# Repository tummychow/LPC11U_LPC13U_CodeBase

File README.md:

# ARM ALARM #

A project to create a better alarm clock and learn some ARM Cortex-M3 development in the process.

## FEATURES ##
- the brain is a powerful ARM Cortex-M3 microcontroller ([NXP LPC1347 in LQFP48](http://www.nxp.com/pip/LPC1347FBD48.html)) which significantly outweighs the average Arduino. I wasn't sure I could do the GUI on an AVR and I don't have much background tying me to that platform, so I figured it was safer to just target a bigger micro.
- sexy touchscreen interface. I'm working with the [Adafruit 2.8" touch TFT](http://adafru.it/376) which has an ILI9325 controller and an exposed 4-wire resistive touchscreen, which I'm controlling with a TI TSC2007.
- high-precision real time clock - an [NXP PCF2129AT](http://www.nxp.com/pip/PCF2129AT.html), which has an integrated TCXO. The existence of the [ChronoDot](http://macetech.com/store/index.php?main_page=product_info&cPath=5&products_id=8) seems to make the Maxim DS3231 more popular (plus the DS3231 is software-compatible with Maxim's popular DS1307), but the code base already supports the NXP part, and it's also half as expensive.
- loud. The alarm sound comes from a buzzer, possibly multiple buzzers. If I was going to settle for speakers, I'd just use my phone.
- [Sick-of-Beige](http://dangerousprototypes.com/docs/Sick_of_Beige_compatible_cases)-style case. Not a standard Sick of Beige size, for cost reasons, but it has the same design.
- various cool software things that I haven't delivered on yet (but plan to eventually)

The schematics are [here](http://github.com/tummychow/arm-alarm/tree/arm-alarm/sch), but the main board schematic is not even vaguely ready to be manufactured, so I'm not going to release it yet. They're in EAGLE 6.5.0 - sorry to KiCAD users. I actually used KiCAD on a school project and might port the schematic there in the future. In the meantime, gerbers and PNG exports are also included for non-EAGLE users.

## STRUCTURE ##
This project is based on a [codebase](http://github.com/microbuilder/LPC11U_LPC13U_CodeBase) by [microbuilder.eu](http://github.com/microbuilder). I've left the `master` and `development` branches of the original repo intact and I won't be doing any work on them, unless I develop something useful that justifies opening a pull request.

My development will take place on the `arm-alarm` branch. I only change the stuff I use, so most of the original code and documentation persists. Any of my dev/feature branches will be prefixed with `aa-` (for example `aa-buzzertest`), so that they don't overlap with the original branches.

The [GitHub page](http://tummychow.github.io/arm-alarm) for the repository serves as a dev blog, so if you really want to know about my progress, you can follow along there. That Jekyll theme is [Lanyon](http://github.com/poole/lanyon) by [Mark Otto](http://github.com/mdo), plus some personal changes from [my fork](http://github.com/tummychow/lanyon).

## BUILDING ##
I'm working with GCC ARM Embedded on a 32-bit Arch Linux virtual machine (installed from the [AUR](http://aur.archlinux.org/packages/gcc-arm-none-eabi/)), so my toolchain is basically the [Makefile](http://github.com/tummychow/arm-alarm/blob/arm-alarm/Makefile) inherited from the original codebase. Refer to the [original documentation](http://github.com/microbuilder/LPC11U_LPC13U_CodeBase/blob/master/doc/toolchain_make.md) for how to use and modify it. Assuming you have everything set up right, `make all` should produce a usable binary. Unless my code is broken, in which case hopefully I'll know.

The board I'm developing for is custom, but in the development process, I'm breadboarding with an LPCXpresso LPC1347 devboard. For $30 with an onboard debugger, you really can't beat the price (unless you use an ST Discovery board - in which case [this](http://github.com/andysworkshop/stm32plus) might help). One caveat you should be aware of, if you intend to use the Makefile for your development like I did, is that the debugger on those boards is closed-source, and to my knowledge, only compatible with one debugging solution (the LPCXpresso IDE, which is free as in beer, but requires registration). You'll have to use the LPCXpresso IDE if you want to use that debugger, even if you aren't developing in that environment.

Since I'm not programming in LPCXpresso and I don't have any other debug hardware, for now I upload the binaries using [Flash Magic](http://www.flashmagictool.com/). A good old FTDI serial adapter will get the job done. The `firmware.hex` binary is the one you want. The LPC1347 also has a ROM bootloader which makes it look like a mass storage device, and you can copy a binary onto it to program the micro. If you do this, you want the `firmware.bin` binary. I believe the Makefile has a `flash` target which does the copying-over; you can program it that way as well.

## CONTRIBUTING ##
I'll cross this bridge when I get to it. But let me say that this project was designed for my very specific alarm-clock-oriented needs, so I doubt it'll be of great interest to others.

## LICENSE ##
My code and schematics are under the [BSD 3-clause license](https://github.com/tummychow/arm-alarm/blob/arm-alarm/License.txt) Refer to the original [README.md](http://github.com/microbuilder/LPC11U_LPC13U_CodeBase/blob/master/README.md) for the licensing terms of the underlying code base (most of which is also BSD 3-clause, but as that readme stipulates, licensing is on a file-by-file basis).

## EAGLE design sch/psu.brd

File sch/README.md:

# Schematic README
Alright, schematic time! I have two schematics but only one is good enough to contemplate manufacture right now, because it's really simple. The other will wait until it's ready.

All schematics are in Eagle 6.5.0. I include all the Eagle files (schematics, board layouts, libraries needed to view them), but I also include Gerbers and exported images in case you don't use Eagle and want to manufacture the board, or just want to see what my work looks like.

The first schematic is the [PSU](http://github.com/tummychow/arm-alarm/blob/arm-alarm/sch/psu.md) which I'm going to use for my project, but I've broken it into an individual board first. The other schematic is for the whole board. I'm not going to put that up until it's in sensible condition and ready to be tested.

## License
I don't really like thinking about licensing too much since it distracts me from the actual design, which I find a lot more fun/relevant/interesting. I have read about some of the differences between open source hardware and software and why they require different licensing schemes. Details about copyrights vs patents, but IANAL so it's not clear to me in the slightest. If you're reading this and know of a helpful link, open an issue about my license choice to let me know!

Anyway, for now, and since I'm not interested in a copyleft license, I'll save myself the confusion and license the schematics/layouts/associated content under the same [BSD 3-clause license](http://github.com/tummychow/arm-alarm/blob/arm-alarm/License.txt) as my code.

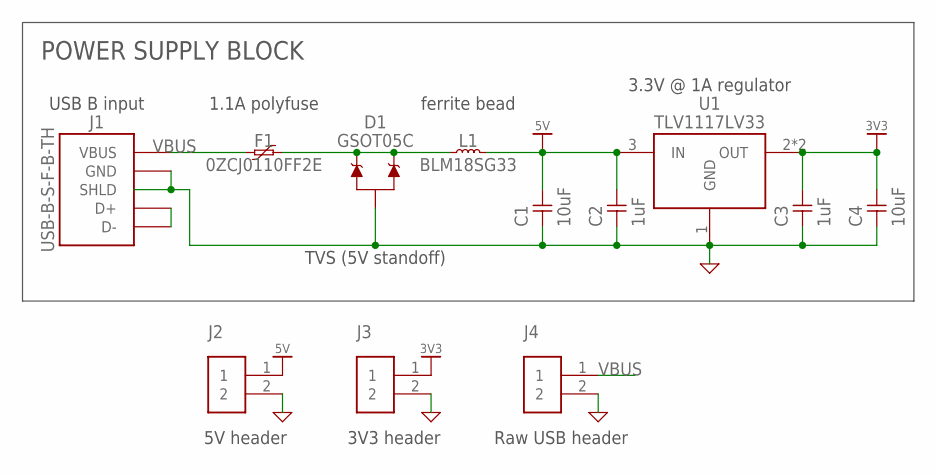
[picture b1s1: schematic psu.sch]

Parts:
C1, C4: 10uF; 0805
C2, C3: 1uF; 0603
D1: GSOT05C; SOT23-3
F1: 0ZCJ0110FF2E; 1206
J1: USB-B-S-F-B-TH; USB-B-SAMTEC
J2, J3, J4: HEADER_100MIL_1ROW_2
L1: BLM18SG33; 0603
U1: TLV1117LV33; SOT223-3

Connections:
3V3: C3.1 (2), C4.1 (2), J3.1, U1.2 (OUT), U1.4 (OUT)
5V: C1.1 (2), C2.1 (2), J2.1, L1.2, U1.3 (IN)
GND: C1.2 (1), C2.2 (1), C3.2 (1), C4.2 (1), D1.3 (A), J1.4 (GND), J1.5 (SHLD), J1.6 (SHLD), J2.2, J3.2, J4.2, U1.1 (GND)
unnamed: J1.2 (D-), J1.3 (D+)
unnamed: D1.1 (C1), D1.2 (C2), F1.2, L1.1
VBUS: F1.1, J1.1 (VBUS), J4.1

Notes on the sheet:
POWER SUPPLY BLOCK
1.1A polyfuse
TVS (5V standoff)
ferrite bead
3.3V @ 1A regulator
USB B input
5V header
3V3 header
Raw USB header

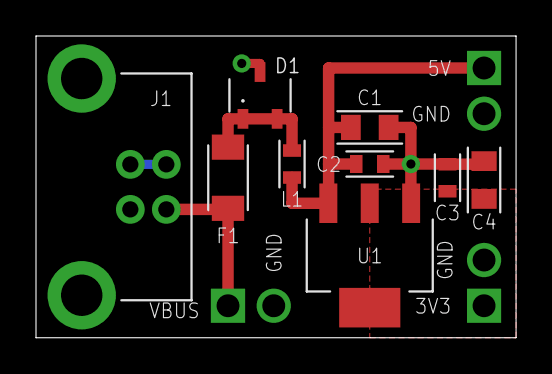
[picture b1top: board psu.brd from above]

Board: 2 copper layers, 26.7 x 16.8 mm, 12 parts (0 on the bottom side), 6 nets.

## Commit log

2014-02-06 add basic .gitignore to prevent tracking binaries
2014-02-06 remove files that my workflow doesn't use
2014-02-06 minor Makefile tweaks
    - enabled GCC ARM Embedded newlib-nano (introduced in arm-gcc 4.7)
    - add lpcrc as dependency of firmware (needed to provide crc for .bin)
    - remove bin/firmware.map with make clean
    - removed trailing spaces on lots of lines
2014-02-10 Add spi_datalayer.o to Makefile
    Resolves linker error in 'SSP0_IRQHandler':
    ssp0_slave.c:81: undefined reference to `spi_DL_slave_state_machine'
    Note: does NOT resolve compiler warning in 'SSP0_IRQHandler':
    ssp0_slave.c:81:5: warning: implicit declaration of function 'spi_DL_slave_state_machine' [-Wimplicit-function-declaration]
2014-02-16 Posted project-status.md (_post)
2014-02-16 Adjusted naming of post list
2014-02-18 Post about PSU schematic
2014-02-18 Implemented changes from Lanyon fork
    See my fork at github.com/tummychow/lanyon for details.
2014-02-24 Post about upcoming Seeed Studio order
2014-03-03 introduce preliminary driver support for ILI9325 LCD controller
    Code was based on existing HX8347G driver, with modifications derived
    from LPC1343 codebase.
    WARNING: as of this commit, this driver has not yet been tested on real
    hardware. There are also some outstanding warnings about left shifts
    exceeding type width (one according to gcc, three according to clang)
    which I have yet to investigate.
2014-03-03 Post about nonstandard case size
2014-03-04 added a readme
2014-03-04 Add preliminary case design
    The files in this commit represent an intermediate design of the acrylic case
    for the project. There are probably a few more changes in store for this part,
    but it's good enough to put online right now.
2014-03-04 Add PSU schematic
    Eagle files, Gerbers and more for the PSU have been added. Refer to included
    dcumentation for more details.
2014-03-16 Fix data pin direction in init
2014-03-16 Init delay adjustments
2014-03-16 Corrected unusual arrangement of clr/set in init
2014-03-16 Experimental GPIO masking on data port
2014-03-16 Extend commands to 16 bits
    Also fixes an oddity in ili9325ReadRegister where it wasn't reading the top 8
    bits of the data.
2014-03-16 Testing screen by toggling colors
2014-03-17 First breadboarding post
2014-04-04 Adjust initiation sequence
    This reflects the sequence in the LPC1343 codebase, which is not quite the
    same as the one in the Adafruit Arduino lib. Maybe this will fix the issues
    I've been seeing.
2014-04-04 Change delays to match LPC1343 codebase
2014-04-04 Remove array looping in init sequence
    Replacing with direct function calls might affect the behavior. Honestly I'm
    just guessing at this point.
2014-04-04 Set CS more often
    In the original LPC1343 implementation, CS would be set between functions and
    cleared when functions began. Before this commit, CS was generally being left
    clear between functions. This should cause CS to be set more rigorously
    between calls, which might have an impact on behavior.
2014-04-04 Fix major typo in reset/backlight pins
    The macros to clear/set the reset pin (and also the backlight pin) were wrong.
    This solves a major part of the init problem I was facing. I'm embarassed to
    admit that I didn't even notice the typo until now.
2014-04-04 Add proper ID checking by querying LCD
2014-04-04 Revert "Set CS more often"
    This reverts commit 56aa25ef9c2110a825ccc1ae345d8da5b361d2e3.
2014-04-04 IT WORKS OH MY GOD
2014-04-04 IT WORKS OH YEAH
